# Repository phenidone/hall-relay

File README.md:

# hall-relay

This is a PCB design for a hall-effect sensor with normally-closed, high-current open-drain output.

The intended purpose is to directly control a low-voltage DC load, e.g. cupboard lighting
or it can be integrated with an alarm or building-management system as a door/window sensor.

The open-drain output is active when a magnetic field is not present, i.e. when the door is open and the magnet is away from this sensor.

## Power Supply

This relay will operate between 5V and 24V DC nominal; the absolute-maximum voltage rating is 28V.  It is not reverse-polarity protected.

It has an open-drain output capable of driving up to 1A into an inductive load (relay or solenoid)
or up to 2A into simple (LED tape) loads.

## Magnet

To shut off the relay, align a magnet pole with the OSHW (gear) logo on the non-component side of the board.

The sensor is omnipolar so it doesn't matter which way the magnet is installed.

## Installation

This sensor should be placed in a door frame with the non-component side of the board exposed to the moving item (door?) that
is to be detected.  Two screw-holes are provided for fixing, and these screws can double as magnetic latching/anchor points.

The PCB assembly must be potted in epoxy after assembly to protect it from moisture.

Connect a 5V-24V isolated plugpack to the + and - terminals.

Connect a DC load (expecting the same voltage as supplied by the plugpack) between the + and OD terminals

## License

This hardware design is (C) 2017 William Brodie-Tyrrell and is licensed under the CERN OHL; see cern_ohl_v_1_2.pdf

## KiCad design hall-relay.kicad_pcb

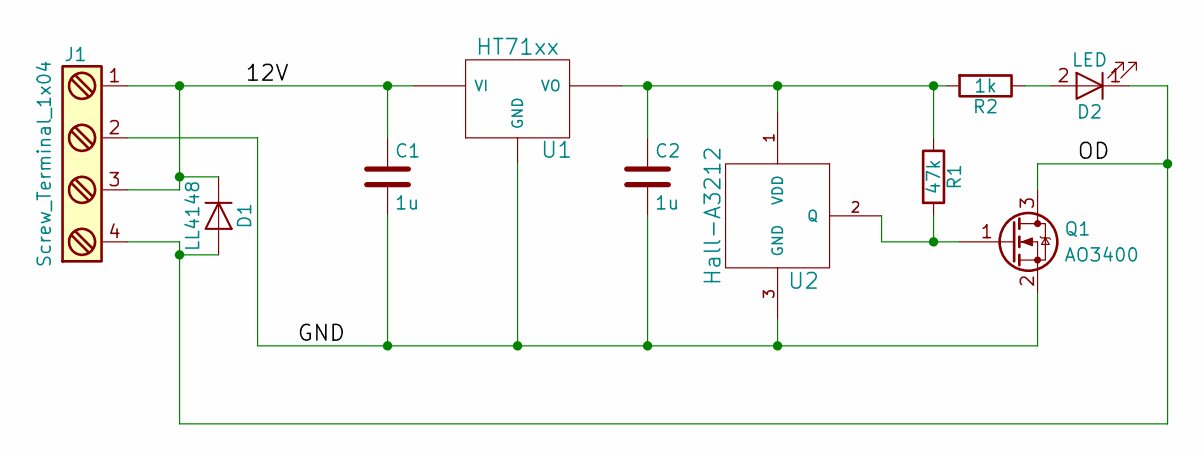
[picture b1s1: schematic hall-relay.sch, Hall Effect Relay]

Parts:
C1, C2: 1u; C_0805
D1: LL4148; D_MiniMELF
D2: LED; LED_0805
J1: Screw_Terminal_1x04; TerminalBlock_Phoenix_MPT-2.54mm_4pol
Q1: AO3400; SOT-23
R1: 47k; R_0805
R2: 1k; R_0805
U1: HT71xx; SOT-89-3
U2: Hall-A3212; SOT-23

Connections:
/12V: C1.1, D1.1 (K), J1.1, J1.3, U1.2 (VI); also elsewhere on the board
/GND: C1.2, C2.2, J1.2, Q1.2 (S), U1.1 (GND), U2.3 (GND)
/OD: D1.2 (A), D2.1 (K), J1.4, Q1.3 (D)
unnamed: C2.1, R1.1, R2.2, U1.3 (VO), U2.1 (VDD)
unnamed 4: D2.2 (A), R2.1; also elsewhere on the board
unnamed: Q1.1 (G), R1.2, U2.2 (Q)

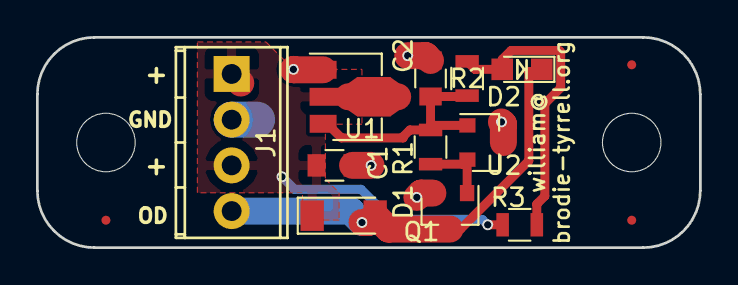
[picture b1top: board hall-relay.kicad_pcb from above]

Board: 2 copper layers, 36.8 x 11.7 mm, 11 parts (0 on the bottom side), 6 nets.

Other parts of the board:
R3: 12k; R_0805

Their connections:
/12V: R3.2; also elsewhere on the board
unnamed 4: R3.1; also elsewhere on the board

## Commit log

2017-12-17 neatened schematic, added PDF
2017-12-18 added LED pullup option to unregulated; avoids LED reverse-breakdown problems
2017-12-18 regenerated schematic pdf
2017-12-19 shortened board to fit panelisation
2017-12-19 fixed README
2018-06-24 moved PCB design to subdirectory, drafted SCAD for a printable 90-deg mounting bracket
2018-06-24 added STL
2018-07-12 made housing a bit shallower
2018-07-18 added 90-degree magnet-mount (non-retained)
2018-07-18 added tiny magnet-retaining tabs so no glue is required.
2018-07-18 added flat magnet-retaining bracket.
